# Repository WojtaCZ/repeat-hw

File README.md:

# REPEAT-HW

A repository containing hardware files (KiCad project) for the REPEAT board

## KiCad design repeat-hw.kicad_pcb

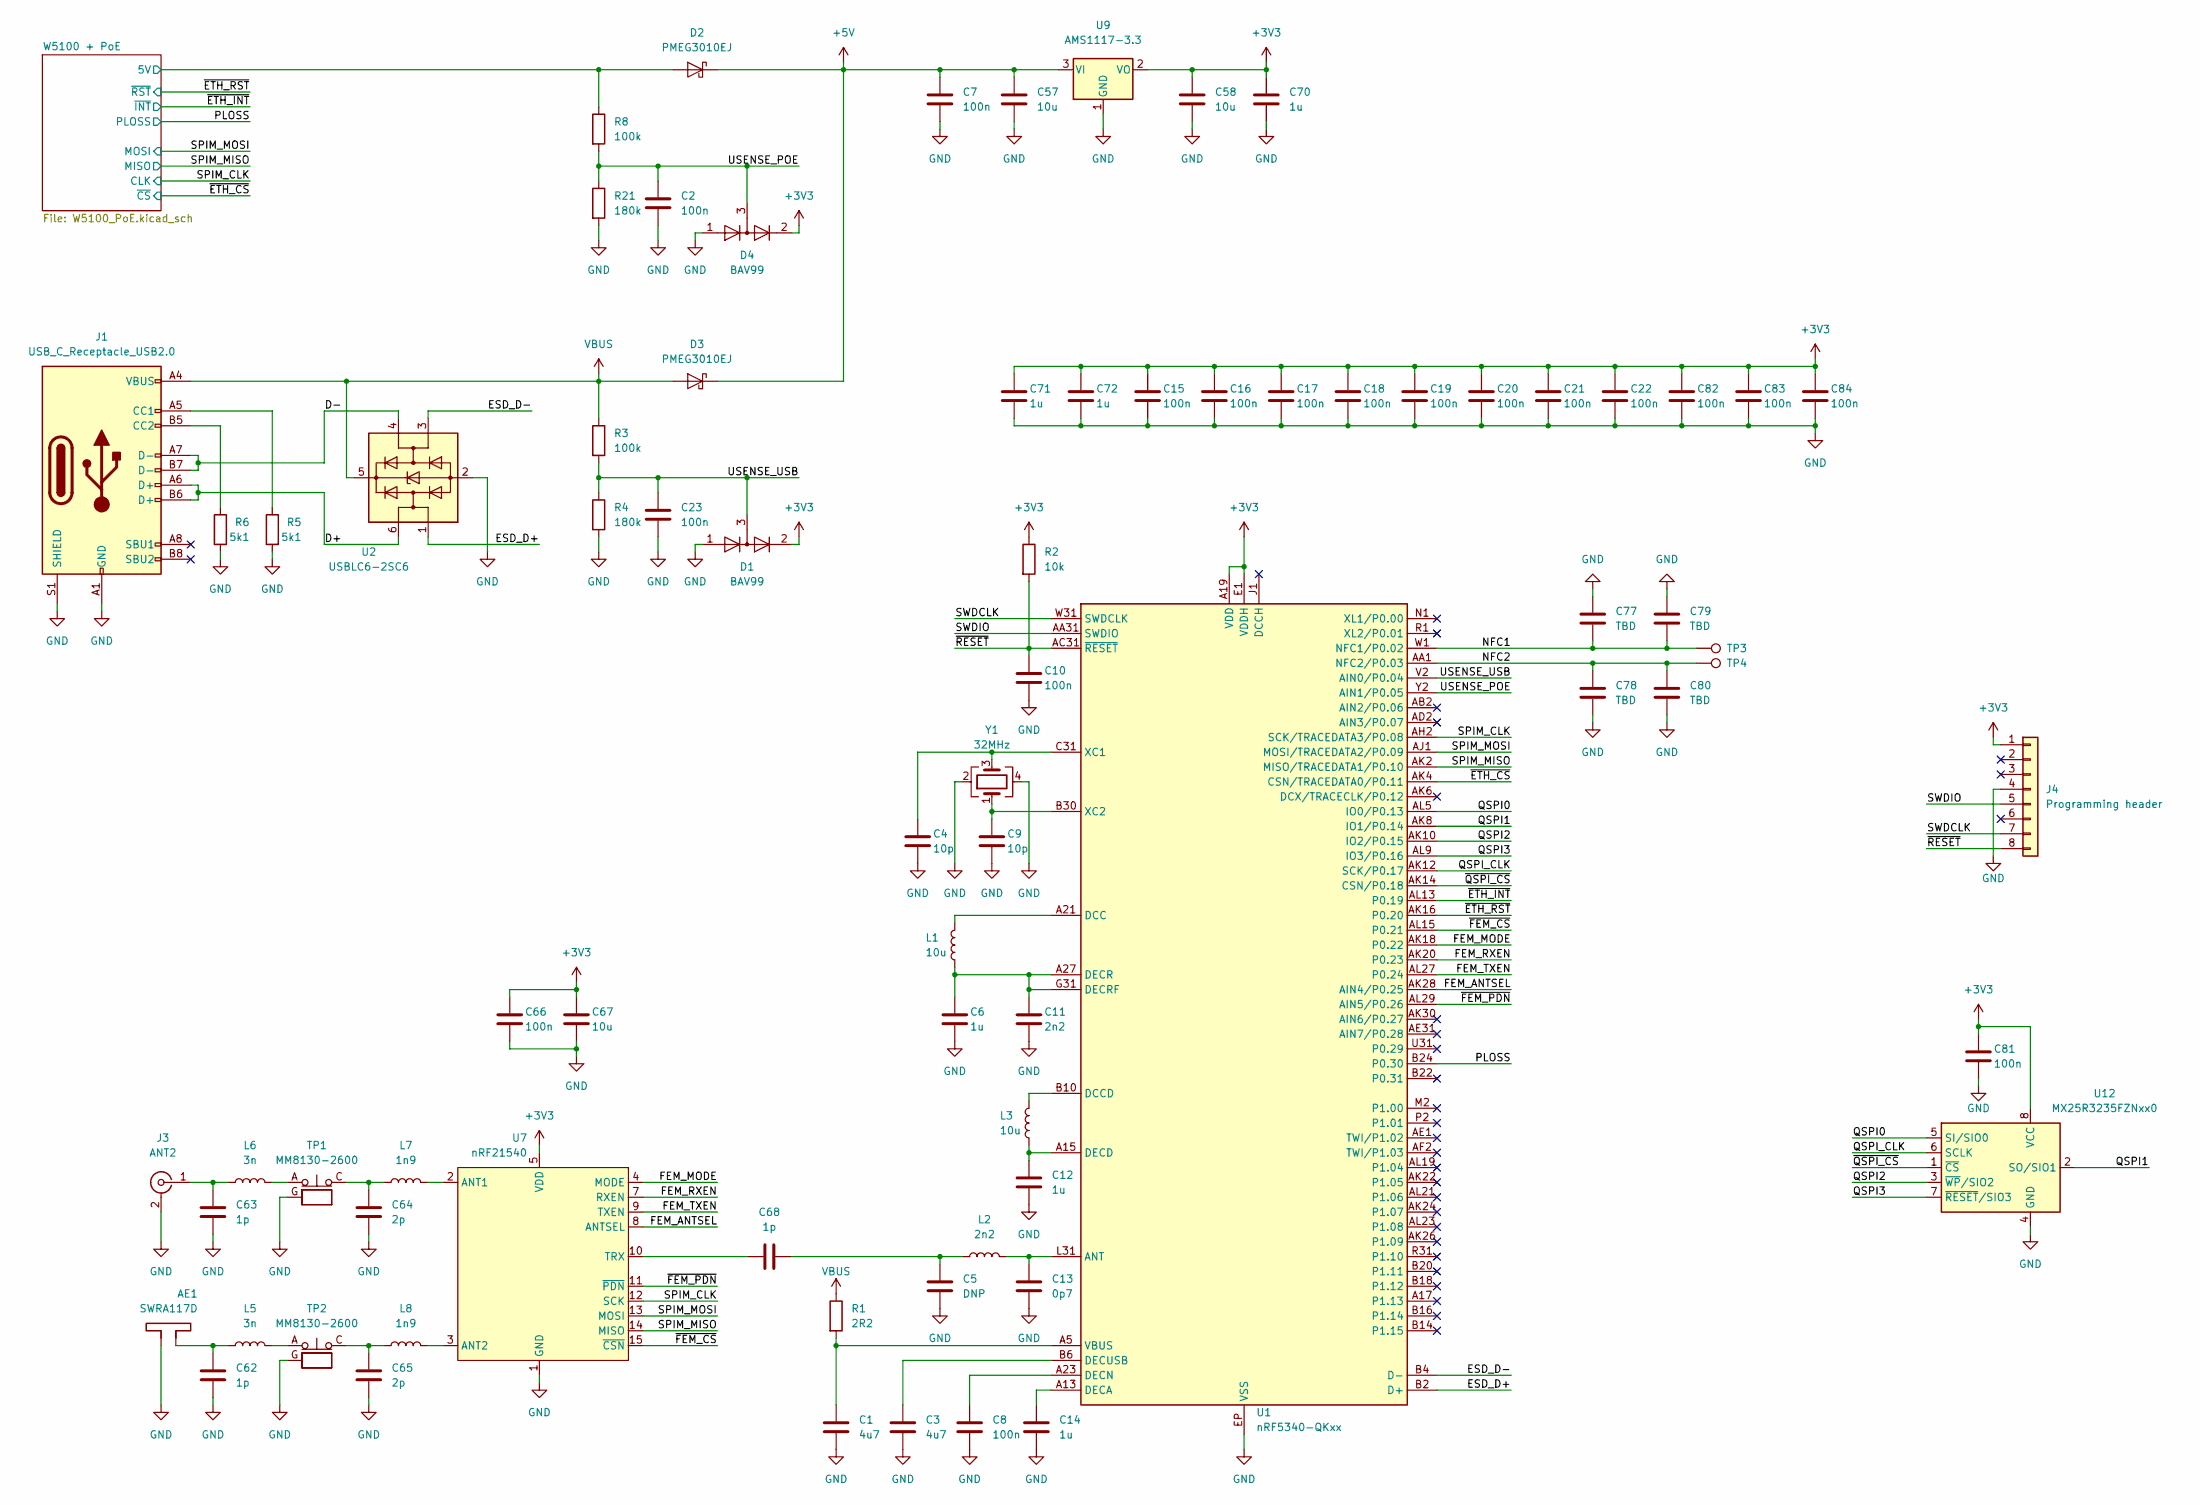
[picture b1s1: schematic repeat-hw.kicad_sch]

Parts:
AE1: SWRA117D; Texas_SWRA117D_2.4GHz_Right
C1, C3: 4u7; C_0603_1608Metric
C2, C7, C8, C10, C15, C16, C17, C18, C19, C20, C21, C22, C23, C66, C81, C82, C83, C84: 100n; C_0402_1005Metric
C4, C9: 10p; C_0402_1005Metric
C5: DNP; C_0402_1005Metric
C6, C12, C14, C70, C71, C72: 1u; C_0603_1608Metric
C11: 2n2; C_0402_1005Metric
C13: 0p7; C_0402_1005Metric
C57, C58: 10u; C_0603_1608Metric
C62, C63, C68: 1p; C_0402_1005Metric
C64, C65: 2p; C_0402_1005Metric
C67: 10u; C_0402_1005Metric
C77, C78, C79, C80: TBD; C_0402_1005Metric
D1, D4: BAV99; SOT-23
D2, D3: PMEG3010EJ; D_SOD-323F
J1: USB_C_Receptacle_USB2.0; USB_C_Receptacle_XKB_U262-16XN-4BVC11
J3: ANT2; U.FL_Hirose_U.FL-R-SMT-1_Vertical
J4: Programming header; SOIC_clipProgSmall
L1, L3: 10u; L_0603_1608Metric
L2: 2n2; C_0402_1005Metric
L5, L6: 3n; C_0402_1005Metric
L7, L8: 1n9; C_0402_1005Metric
R1: 2R2; R_0402_1005Metric
R2: 10k; R_0402_1005Metric
R3, R8: 100k; R_0402_1005Metric
R4, R21: 180k; R_0402_1005Metric
R5, R6: 5k1; R_0402_1005Metric
TP1, TP2: MM8130-2600
TP3, TP4: TestPoint; TestPoint_Pad_D1.0mm
U1: nRF5340-QKxx; Nordic_AQFN-94-1EP_7x7mm_P0.4mm
U2: USBLC6-2SC6; SOT-23-6
U7: nRF21540; QFN-16-1EP_4x4mm_P0.65mm_EP2.7x2.7mm_ThermalVias
U9: AMS1117-3.3; SOT-223-3_TabPin2
U12: MX25R3235FZNxx0; WSON-8-1EP_6x5mm_P1.27mm_EP3.4x4mm
Y1: 32MHz; Crystal_SMD_3225-4Pin_3.2x2.5mm

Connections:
+3V3: C15.1, C16.1, C17.1, C18.1, C19.1, C20.1, C21.1, C22.1, C58.1, C66.1, C67.1, C70.1, C71.1, C72.1, C81.1, C82.1, C83.1, C84.1, D1.2 (A), D4.2 (A), J4.1, R2.1, U1.A19 (VDD), U1.AC1 (VDD), U1.AG1 (VDD), U1.AJ31 (VDD), U1.AL3 (VDD), U1.AL7 (VDD), U1.AL11 (VDD), U1.AL17 (VDD), U1.AL25 (VDD), U1.B8 (VDD), U1.B28 (VDD), U1.C1 (VDD), U1.E1 (VDDH), U1.E31 (VDD), U1.L1 (VDD), U1.N31 (VDD), U1.U1 (VDD), U7.5 (VDD), U7.6 (VDD), U9.2 (VO), U12.8 (VCC); also elsewhere on the board
+5V: C7.1, C57.1, D2.1 (K), D3.1 (K), U9.3 (VI)
/D+: J1.A6 (D+), J1.B6 (D+), U2.6 (I/O1)
/D-: J1.A7 (D-), J1.B7 (D-), U2.4 (I/O2)
/ESD_D+: U1.B2 (D+), U2.1 (I/O1)
/ESD_D-: U1.B4 (D-), U2.3 (I/O2)
/FEM_ANTSEL: U1.AK28 (AIN4/P0.25), U7.8 (ANTSEL)
/FEM_MODE: U1.AK18 (P0.22), U7.4 (MODE)
/FEM_RXEN: U1.AK20 (P0.23), U7.7 (RXEN)
/FEM_TXEN: U1.AL27 (P0.24), U7.9 (TXEN)
/NFC1: C77.2, C79.2, TP3.1, U1.W1 (NFC1/P0.02)
/NFC2: C78.1, C80.1, TP4.1, U1.AA1 (NFC2/P0.03)
/PLOSS: U1.B24 (P0.30); also elsewhere on the board
/QSPI0: U1.AL5 (IO0/P0.13), U12.5 (SI/SIO0)
/QSPI1: U1.AK8 (IO1/P0.14), U12.2 (SO/SIO1)
/QSPI2: U1.AK10 (IO2/P0.15), U12.3 (~WP/SIO2)
/QSPI3: U1.AL9 (IO3/P0.16), U12.7 (~RESET/SIO3)
/QSPI_CLK: U1.AK12 (SCK/P0.17), U12.6 (SCLK)
/SPIM_CLK: U1.AH2 (SCK/TRACEDATA3/P0.08), U7.12 (SCK); also elsewhere on the board
/SPIM_MISO: U1.AK2 (MISO/TRACEDATA1/P0.10), U7.14 (MISO); also elsewhere on the board
/SPIM_MOSI: U1.AJ1 (MOSI/TRACEDATA2/P0.09), U7.13 (MOSI); also elsewhere on the board
/SWDCLK: J4.7, U1.W31 (SWDCLK)
/SWDIO: J4.5, U1.AA31 (SWDIO)
/USENSE_POE: C2.1, D4.3 (K), R8.2, R21.1, U1.Y2 (AIN1/P0.05)
/USENSE_USB: C23.1, D1.3 (K), R3.2, R4.1, U1.V2 (AIN0/P0.04)
/W5100 + PoE/5V: D2.2 (A), R8.1; also elsewhere on the board
/~ETH_CS: U1.AK4 (CSN/TRACEDATA0/P0.11); also elsewhere on the board
/~ETH_INT: U1.AL13 (P0.19); also elsewhere on the board
/~ETH_RST: U1.AK16 (P0.20); also elsewhere on the board
/~FEM_CS: U1.AL15 (P0.21), U7.15 (~CSN)
/~FEM_PDN: U1.AL29 (AIN5/P0.26), U7.11 (~PDN)
/~QSPI_CS: U1.AK14 (CSN/P0.18), U12.1 (~CS)
/~RESET: C10.1, J4.8, R2.2, U1.AC31 (~RESET)
GND: AE1.2, C1.2, C2.2, C3.2, C4.2, C5.2, C6.2, C7.2, C8.2, C9.2, C10.2, C11.2, C12.2, C13.2, C14.2, C15.2, C16.2, C17.2, C18.2, C19.2, C20.2, C21.2, C22.2, C23.2, C57.2, C58.2, C62.2, C63.2, C64.2, C65.2, C66.2, C67.2, C70.2, C71.2, C72.2, C77.1, C78.2, C79.1, C80.2, C81.2, C82.2, C83.2, C84.2, D1.1 (K), D4.1 (K), J1.A1 (GND), J1.A12 (GND), J1.B1 (GND), J1.B12 (GND), J1.S1 (SHIELD), J3.2 (Ext), J4.4, R4.2, R5.2, R6.2, R21.2, TP1.G, TP2.G, U1.EP (VSS), U2.2 (GND), U7.1 (GND), U7.16 (GND), U7.17 (GND), U9.1 (GND), U12.4 (GND), U12.9 (GND), Y1.2, Y1.4; also elsewhere on the board
unnamed: AE1.1, C62.1, L5.1
unnamed: C1.1, R1.2, U1.A5 (VBUS)
unnamed: C3.1, U1.B6 (DECUSB)
unnamed: C4.1, U1.C31 (XC1), Y1.3
unnamed: C5.1, C68.2, L2.1
unnamed: C8.1, U1.A23 (DECN)
unnamed: C9.1, U1.B30 (XC2), Y1.1
unnamed: C6.1, C11.1, L1.1, U1.A27 (DECR), U1.G31 (DECRF)
unnamed: C12.1, L3.1, U1.A15 (DECD)
unnamed: C13.1, L2.2, U1.L31 (ANT)
unnamed: C14.1, U1.A13 (DECA)
unnamed: C63.1, J3.1 (In), L6.1
unnamed: C64.1, L7.1, TP1.C
unnamed: C65.1, L8.1, TP2.C
unnamed: C68.1, U7.10 (TRX)
unnamed: J1.A5 (CC1), R5.1
unnamed: J1.B5 (CC2), R6.1
unnamed: L1.2, U1.A21 (DCC)
unnamed: L3.2, U1.B10 (DCCD)
unnamed: L5.2, TP2.A
unnamed: L6.2, TP1.A
unnamed: L7.2, U7.2 (ANT1)
unnamed: L8.2, U7.3 (ANT2)
VBUS: D3.2 (A), J1.A4 (VBUS), J1.A9 (VBUS), J1.B4 (VBUS), J1.B9 (VBUS), R1.1, R3.1, U2.5 (VBUS)

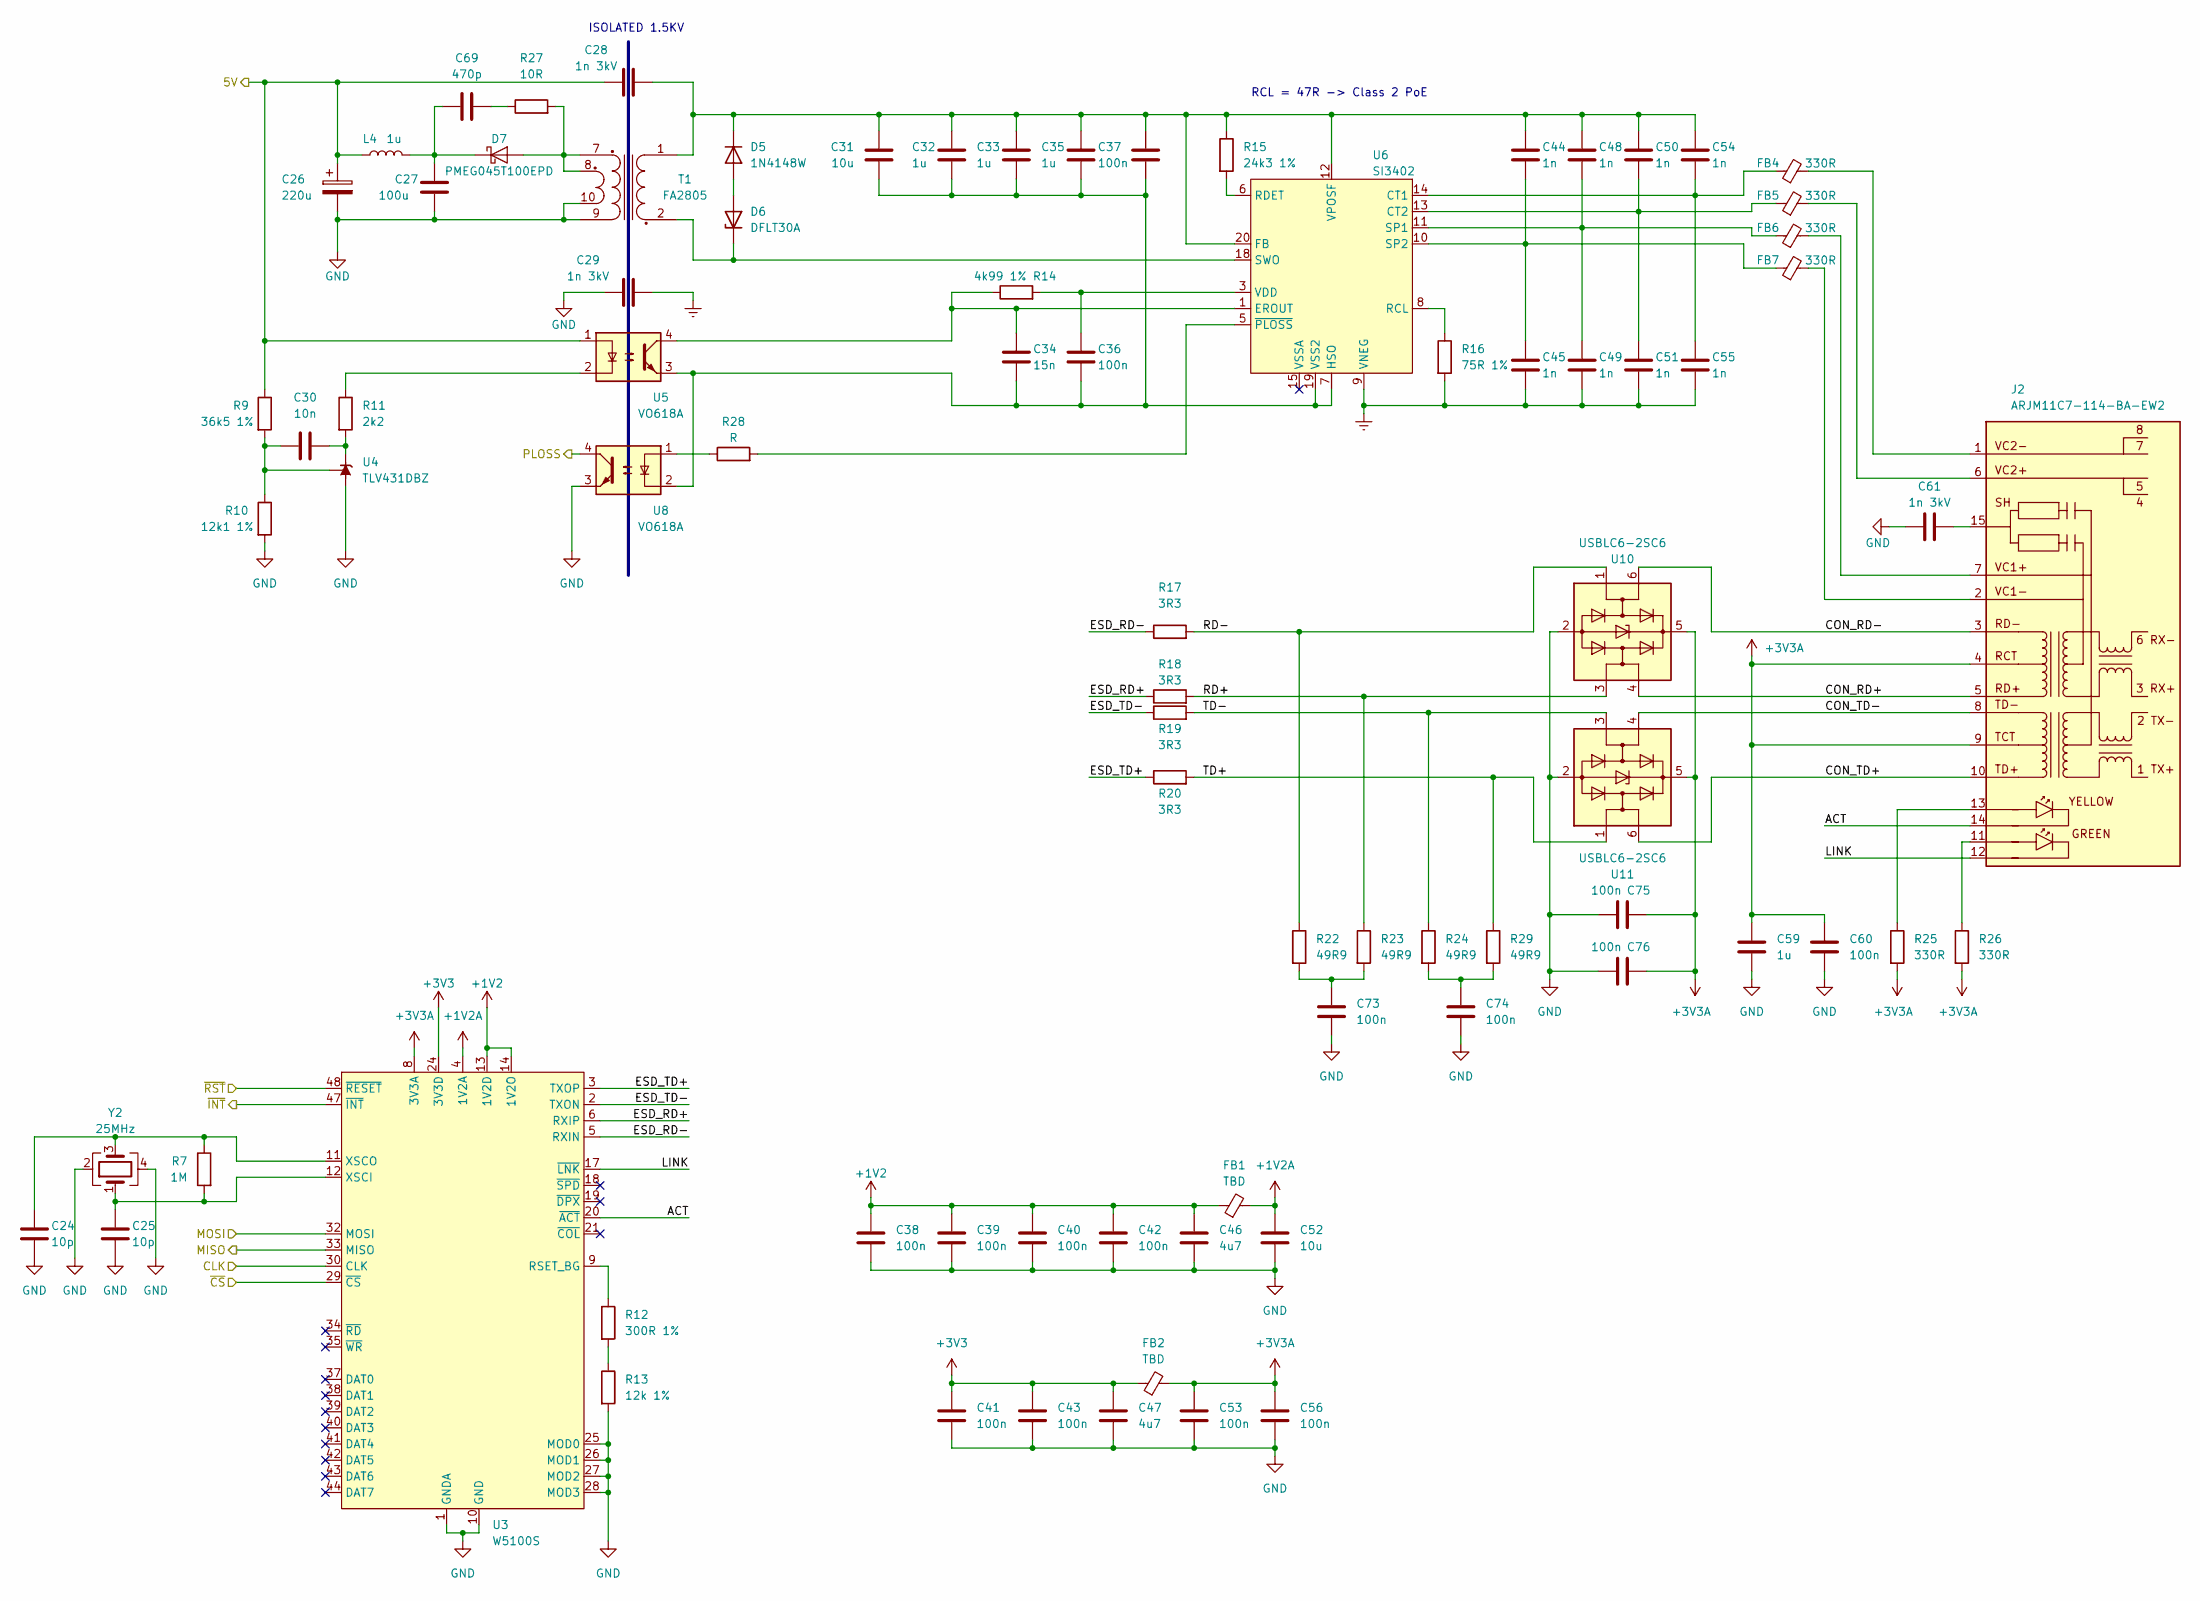
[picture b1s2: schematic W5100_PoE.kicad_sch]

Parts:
C24, C25: 10p; C_0402_1005Metric
C26: 220u; CP_Elec_5x5.3
C27: 100u; C_1206_3216Metric
C28, C29, C61: 1n 3kV; C_1206_3216Metric
C30: 10n; C_0402_1005Metric
C31, C52: 10u; C_0603_1608Metric
C32, C33, C35, C59: 1u; C_0603_1608Metric
C34: 15n; C_0402_1005Metric
C36, C37, C38, C39, C40, C41, C42, C43, C53, C56, C60, C73, C74, C75, C76: 100n; C_0402_1005Metric
C44, C45, C48, C49, C50, C51, C54, C55: 1n; C_0402_1005Metric
C46, C47: 4u7; C_0603_1608Metric
C69: 470p; C_0402_1005Metric
D5: 1N4148W; D_SOD-123
D6: DFLT30A; D_PowerDI-123
D7: PMEG045T100EPD; Nexperia_CFP15_SOT-1289
FB1, FB2: TBD; C_0402_1005Metric
FB4, FB5, FB6, FB7: 330R; L_0805_2012Metric
J2: ARJM11C7-114-BA-EW2
L4: 1u; C_0603_1608Metric
R7: 1M; R_0402_1005Metric
R9: 36k5 1%; R_0402_1005Metric
R10: 12k1 1%; R_0402_1005Metric
R11: 2k2; R_0402_1005Metric
R12: 300R 1%; R_0402_1005Metric
R13: 12k 1%; R_0402_1005Metric
R14: 4k99 1%; R_0402_1005Metric
R15: 24k3 1%; R_0402_1005Metric
R16: 75R 1%; R_0402_1005Metric
R17, R18, R19, R20: 3R3; R_0402_1005Metric
R22, R23, R24, R29: 49R9; R_0402_1005Metric
R25, R26: 330R; R_0402_1005Metric
R27: 10R; R_0402_1005Metric
R28: R; R_0402_1005Metric
T1: FA2805; Transformer_Coilcraft_Si3402
U3: W5100S; QFN-48-1EP_7x7mm_P0.5mm_EP5.3x5.3mm
U4: TLV431DBZ; SOT-23
U5, U8: VO618A; SO-4_7.6x3.6mm_P2.54mm
U6: SI3402; Skyworks_QFN-20_1EP5x5mm_P0.8mm_EP2.7x2.7mm
U10, U11: USBLC6-2SC6; SOT-23-6
Y2: 25MHz; Crystal_SMD_3225-4Pin_3.2x2.5mm

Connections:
+1V2: C38.1, C39.1, C40.1, C42.1, C46.1, FB1.1, U3.13 (1V2D), U3.14 (1V2O), U3.22 (1V2D), U3.31 (1V2D), U3.45 (1V2D)
+1V2A: C52.1, FB1.2, U3.4 (1V2A)
+3V3: C41.1, C43.1, C47.1, FB2.1, U3.24 (3V3D), U3.36 (3V3D); also elsewhere on the board
+3V3A: C53.1, C56.1, C59.1, C60.1, C75.2, C76.2, FB2.2, J2.4, J2.9, R25.2, R26.2, U3.8 (3V3A), U3.15 (3V3A), U10.5 (VBUS), U11.5 (VBUS)
/PLOSS: U8.4; also elsewhere on the board
/SPIM_CLK: U3.30 (CLK); also elsewhere on the board
/SPIM_MISO: U3.33 (MISO); also elsewhere on the board
/SPIM_MOSI: U3.32 (MOSI); also elsewhere on the board
/W5100 + PoE/5V: C26.1, C28.1, L4.1, R9.1, U5.1; also elsewhere on the board
/W5100 + PoE/ACT: J2.14, U3.20 (~ACT)
/W5100 + PoE/CON_RD+: J2.5, U10.4 (I/O2)
/W5100 + PoE/CON_RD-: J2.3, U10.6 (I/O1)
/W5100 + PoE/CON_TD+: J2.10, U11.6 (I/O1)
/W5100 + PoE/CON_TD-: J2.8, U11.4 (I/O2)
/W5100 + PoE/ESD_RD+: R18.1, U3.6 (RXIP)
/W5100 + PoE/ESD_RD-: R17.1, U3.5 (RXIN)
/W5100 + PoE/ESD_TD+: R20.1, U3.3 (TXOP)
/W5100 + PoE/ESD_TD-: R19.1, U3.2 (TXON)
/W5100 + PoE/LINK: J2.12, U3.17 (~LNK)
/W5100 + PoE/RD+: R18.2, R23.1, U10.3 (I/O2)
/W5100 + PoE/RD-: R17.2, R22.1, U10.1 (I/O1)
/W5100 + PoE/TD+: R20.2, R29.1, U11.1 (I/O1)
/W5100 + PoE/TD-: R19.2, R24.1, U11.3 (I/O2)
/~ETH_CS: U3.29 (~CS); also elsewhere on the board
/~ETH_INT: U3.47 (~INT); also elsewhere on the board
/~ETH_RST: U3.48 (~RESET); also elsewhere on the board
Earth: C29.2, C45.2, C49.2, C51.2, C55.2, R16.2, U6.9 (VNEG), U6.21 (VNEG)
GND: C24.2, C25.2, C26.2, C27.2, C29.1, C38.2, C39.2, C40.2, C41.2, C42.2, C43.2, C46.2, C47.2, C52.2, C53.2, C56.2, C59.2, C60.2, C61.1, C73.2, C74.2, C75.1, C76.1, R10.2, R13.2, T1.9, T1.10, U3.1 (GNDA), U3.7 (GNDA), U3.10 (GND), U3.16 (GNDA), U3.23 (GND), U3.25 (MOD0), U3.26 (MOD1), U3.27 (MOD2), U3.28 (MOD3), U3.46 (GND), U3.49 (GND), U4.3 (A), U8.3, U10.2 (GND), U11.2 (GND), Y2.2, Y2.4; also elsewhere on the board
unnamed: C24.1, R7.1, U3.11 (XSCO), Y2.3
unnamed: C25.1, R7.2, U3.12 (XSCI), Y2.1
unnamed: C27.1, C69.1, D7.3 (K), L4.2
unnamed: C28.2, C31.1, C32.1, C33.1, C35.1, C37.1, C44.1, C48.1, C50.1, C54.1, D5.1 (K), R15.1, T1.1, U6.12 (VPOSF), U6.20 (FB)
unnamed: C30.1, R9.2, R10.1, U4.2 (REF)
unnamed: C30.2, R11.2, U4.1 (K)
unnamed: C31.2, C32.2, C33.2, C34.2, C35.2, C36.2, C37.2, U5.3, U6.7 (HSO), U6.19 (VSS2), U8.2
unnamed: C34.1, R14.1, U5.4, U6.1 (EROUT)
unnamed: C36.1, R14.2, U6.3 (VDD)
unnamed: C44.2, C45.1, FB7.1, U6.10 (SP2)
unnamed: C48.2, C49.1, FB6.1, U6.11 (SP1)
unnamed: C50.2, C51.1, FB5.1, U6.13 (CT2)
unnamed: C54.2, C55.1, FB4.1, U6.14 (CT1)
unnamed: C61.2, J2.15
unnamed: C69.2, R27.1
unnamed: C73.1, R22.2, R23.2
unnamed: C74.1, R24.2, R29.2
unnamed: D5.2 (A), D6.2 (A)
unnamed: D6.1 (K), T1.2, U6.18 (SWO)
unnamed: D7.1 (A), D7.2 (A), R27.2, T1.7, T1.8
unnamed: FB4.2, J2.1
unnamed: FB5.2, J2.6
unnamed: FB6.2, J2.7
unnamed: FB7.2, J2.2
unnamed: J2.11, R26.1
unnamed: J2.13, R25.1
unnamed: R11.1, U5.2
unnamed: R12.1, U3.9 (RSET_BG)
unnamed: R12.2, R13.1
unnamed: R15.2, U6.6 (RDET)
unnamed: R16.1, U6.8 (RCL)
unnamed: R28.1, U8.1
unnamed: R28.2, U6.5 (~PLOSS)

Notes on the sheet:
ISOLATED 1.5KV
RCL = 47R -> Class 2 PoE

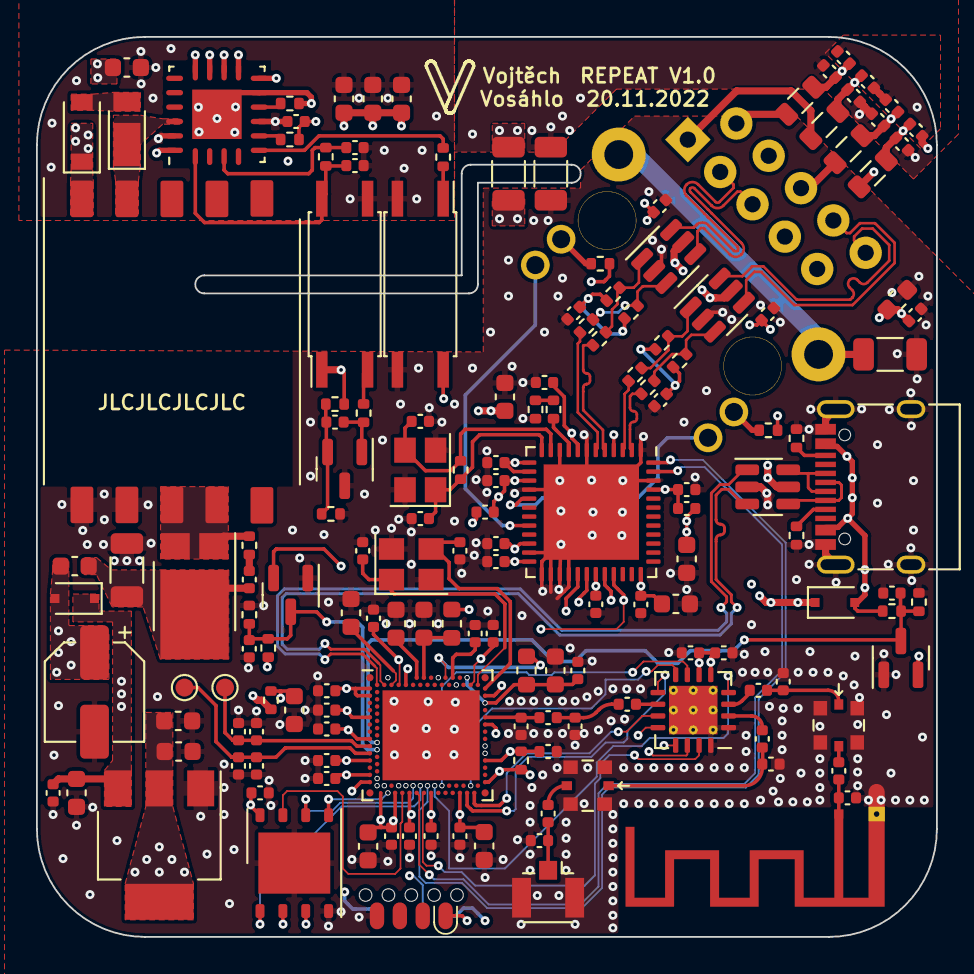
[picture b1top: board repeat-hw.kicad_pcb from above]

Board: 6 copper layers, 50.0 x 50.0 mm, 158 parts (1 on the bottom side), 109 nets.

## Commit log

2022-10-17 added W5100
2022-10-17 Added RJ45
2022-10-23 Finishe PoE and ethernet
2022-10-25 Added USB port
2022-10-26 Polished schematic
2022-10-26 Hopefully finished schematic
2022-11-19 Routing half done
2022-11-19 More routing
2022-11-20 Routing almost done
2022-11-20 Routing done
2022-11-20 Updated schematic
2022-11-24 Finalized for production
2022-11-26 Changed via to copper clearance to correct value
2023-11-19 Sync
2023-11-19 Clean up
2023-11-19 Added readme
